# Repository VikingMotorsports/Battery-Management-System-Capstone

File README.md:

# VMS Battery Management Capstone 2026 Repo

All System Architecture KiCAD Schematics and GERBER files along with the zephyr firmware C code.

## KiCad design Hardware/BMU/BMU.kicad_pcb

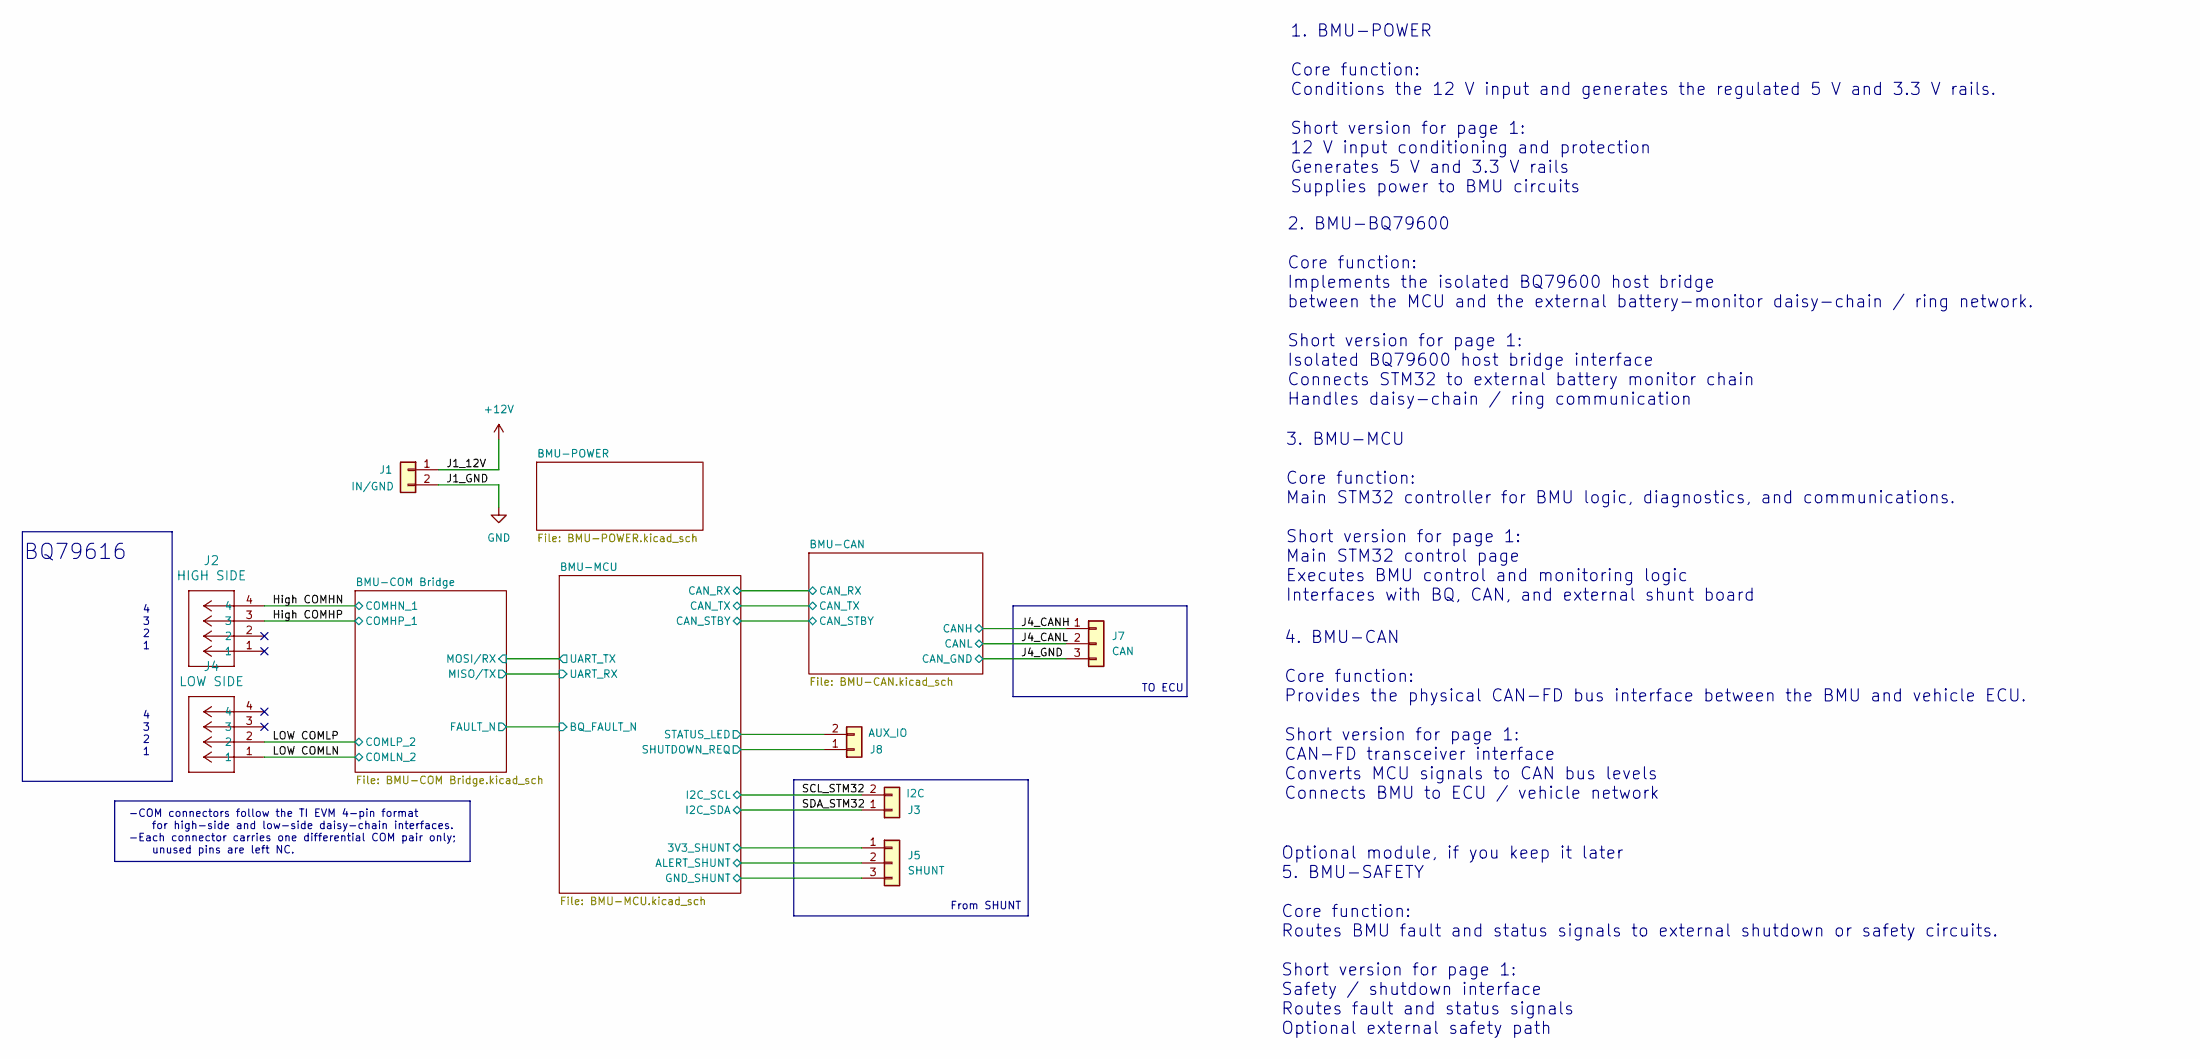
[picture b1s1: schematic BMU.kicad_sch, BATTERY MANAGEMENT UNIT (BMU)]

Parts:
J1: IN/GND; PinHeader_1x02_P2.54mm_Vertical
J2: HIGH SIDE; CONN_70551-xxxx_04_MOL
J3: I2C; PinHeader_1x02_P2.54mm_Vertical
J4: LOW SIDE; CONN_70551-xxxx_04_MOL
J5: SHUNT; PinHeader_1x03_P2.54mm_Vertical
J7: CAN; PinHeader_1x03_P2.54mm_Vertical
J8: AUX_IO; PinHeader_1x02_P2.54mm_Vertical

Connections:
+3V3: J5.1; also elsewhere on the board
+12V: J1.1; also elsewhere on the board
/BMU-MCU/ALERT_SHUNT: J5.2; also elsewhere on the board
/BMU-MCU/SHUTDOWN_REQ: J8.1; also elsewhere on the board
/BMU-MCU/STATUS_LED: J8.2; also elsewhere on the board
/High COMHN: J2.4; also elsewhere on the board
/High COMHP: J2.3; also elsewhere on the board
/J4_CANH: J7.1; also elsewhere on the board
/J4_CANL: J7.2; also elsewhere on the board
/LOW COMLN: J4.1; also elsewhere on the board
/LOW COMLP: J4.2; also elsewhere on the board
/SCL_STM32: J3.2; also elsewhere on the board
/SDA_STM32: J3.1; also elsewhere on the board
GND: J1.2, J5.3, J7.3; also elsewhere on the board

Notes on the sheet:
4 3 2 1
2. BMU-BQ79600 Core function: Implements the isolated BQ79600 host bridge between the MCU and the external battery-monitor daisy-chain / ring network. Short version for page 1: Isolated BQ79600 host bridge interface Connects STM32 to external battery monitor chain Handles daisy-chain / ring communi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
-COM connectors follow the TI EVM 4-pin format for high-side and low-side daisy-chain interfaces. -Each connector carries one differential COM pair only; unused pins are left NC.
4. BMU-CAN Core function: Provides the physical CAN-FD bus interface between the BMU and vehicle ECU. Short version for page 1: CAN-FD transceiver interface Converts MCU signals to CAN bus levels Connects BMU to ECU / vehicle network
3. BMU-MCU Core function: Main STM32 controller for BMU logic, diagnostics, and communications. Short version for page 1: Main STM32 control page Executes BMU control and monitoring logic Interfaces with BQ, CAN, and external shunt board
TO ECU
1. BMU-POWER Core function: Conditions the 12 V input and generates the regulated 5 V and 3.3 V rails. Short version for page 1: 12 V input conditioning and protection Generates 5 V and 3.3 V rails Supplies power to BMU circuits
From SHUNT
BQ79616
Optional module, if you keep it later 5. BMU-SAFETY Core function: Routes BMU fault and status signals to external shutdown or safety circuits. Short version for page 1: Safety / shutdown interface Routes fault and status signals Optional external safety path

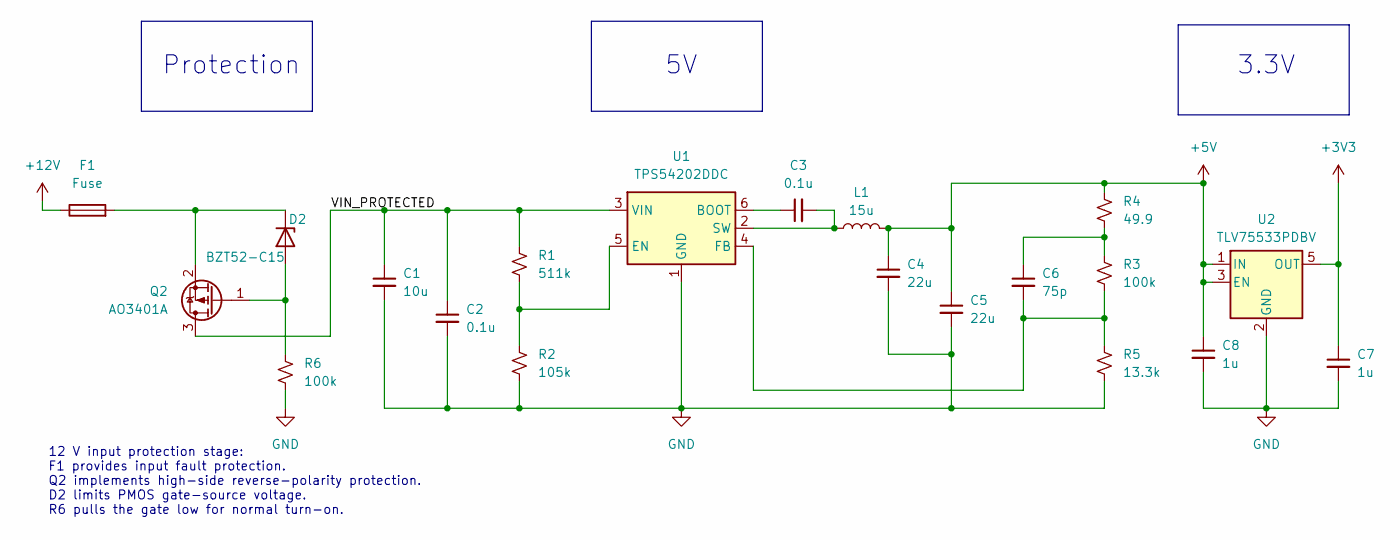
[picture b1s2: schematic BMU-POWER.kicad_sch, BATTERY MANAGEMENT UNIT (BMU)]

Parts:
C1: 10u; C_1206_3216Metric
C2, C3: 0.1u; C_0805_2012Metric
C4, C5: 22u; C_1206_3216Metric
C6: 75p; C_0805_2012Metric
C7, C8: 1u; C_0805_2012Metric
D2: BZT52-C15; D_SOD-123
F1: Fuse; Fuse_1206_3216Metric
L1: 15u; L_7.3x7.3_H4.5
Q2: AO3401A; SOT-23
R1: 511k; R_0805_2012Metric
R2: 105k; R_0805_2012Metric
R3, R6: 100k; R_0805_2012Metric
R4: 49.9; R_0805_2012Metric
R5: 13.3k; R_0805_2012Metric
U1: TPS54202DDC; SOT-23-6
U2: TLV75533PDBV; SOT-23-5

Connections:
+3V3: C7.1, U2.5 (OUT); also elsewhere on the board
+5V: C4.1, C5.1, C8.1, L1.2, R4.1, U2.1 (IN), U2.3 (EN); also elsewhere on the board
+12V: F1.1; also elsewhere on the board
/BMU-POWER/VIN_PROTECTED: C1.1, C2.1, Q2.3 (D), R1.1, U1.3 (VIN)
GND: C1.2, C2.2, C4.2, C5.2, C7.2, C8.2, R2.2, R5.2, R6.2, U1.1 (GND), U2.2 (GND); also elsewhere on the board
unnamed: C6.1, R3.1, R4.2
unnamed: D2.2 (A), Q2.1 (G), R6.1
unnamed: D2.1 (K), F1.2, Q2.2 (S)
unnamed: C3.1, U1.6 (BOOT)
unnamed: R1.2, R2.1, U1.5 (EN)
unnamed: C6.2, R3.2, R5.1, U1.4 (FB)
unnamed: C3.2, L1.1, U1.2 (SW)

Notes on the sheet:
3.3V
Protection
12 V input protection stage: F1 provides input fault protection. Q2 implements high-side reverse-polarity protection. D2 limits PMOS gate-source voltage. R6 pulls the gate low for normal turn-on.

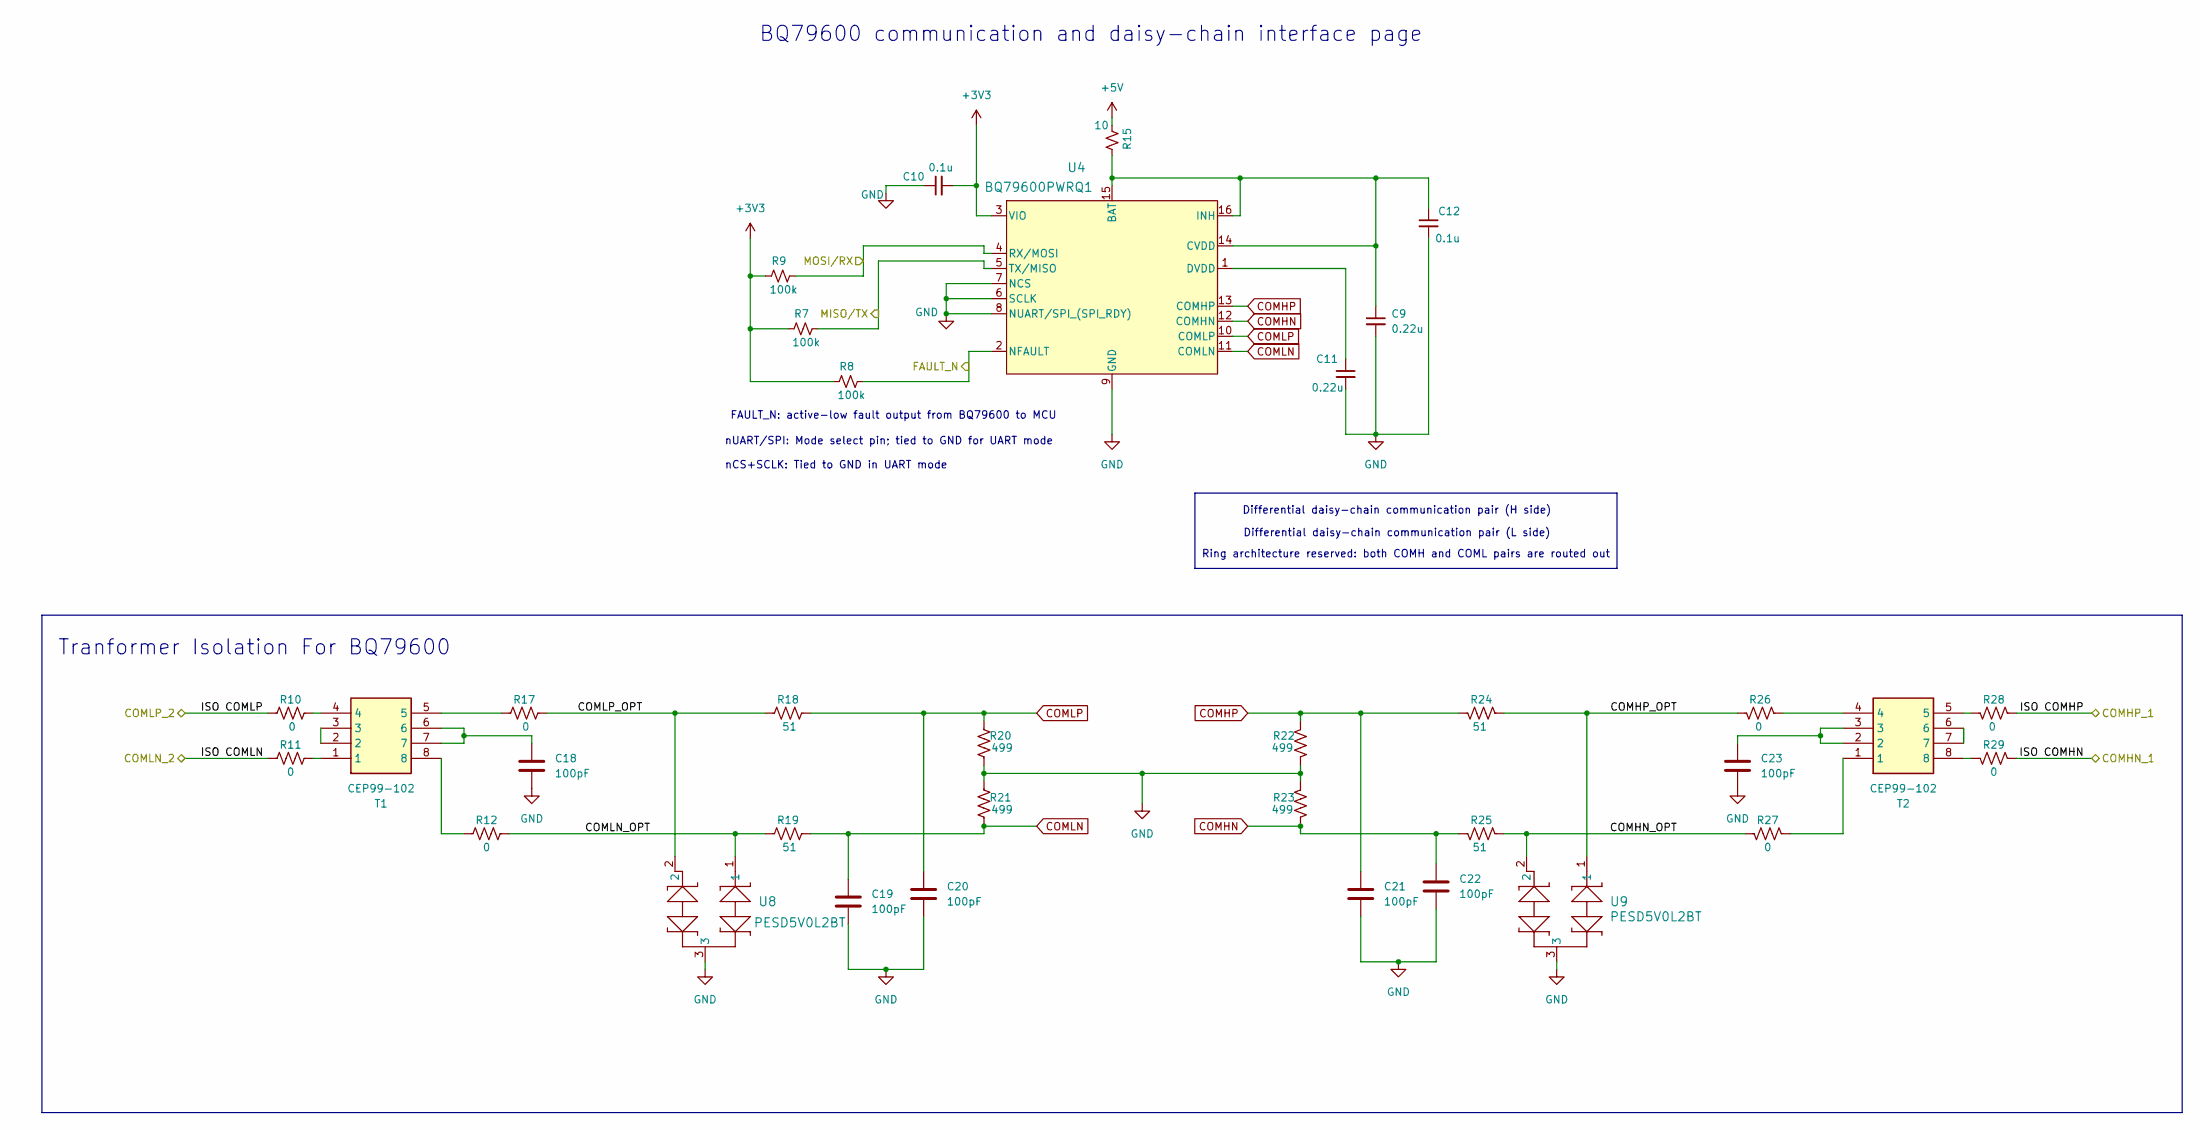
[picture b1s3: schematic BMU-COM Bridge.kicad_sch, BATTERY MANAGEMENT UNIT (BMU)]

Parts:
C9, C11: 0.22u; C_0805_2012Metric
C10, C12: 0.1u; C_0805_2012Metric
C18, C19, C20, C21, C22, C23: 100pF; C_0805_2012Metric
R7, R8, R9: 100k; R_0805_2012Metric
R10, R11, R12, R17, R26, R27, R28, R29: 0; R_0805_2012Metric
R15: 10; R_0805_2012Metric
R18, R19, R24, R25: 51; R_0805_2012Metric
R20, R21, R22, R23: 499; R_0805_2012Metric
T1, T2: CEP99-102; CEP99102; Manufacturer_Part_Number CEP99-102
U4: BQ79600PWRQ1; TSSOP16_PW_TEX
U8, U9: PESD5V0L2BT; SOT23_NEX

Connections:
+3V3: C10.2, R7.1, R8.1, R9.1, U4.3 (VIO); also elsewhere on the board
+5V: R15.1; also elsewhere on the board
/BMU-COM Bridge/COMHN_OPT: R25.1, R27.2, U9.2
/BMU-COM Bridge/COMHP_OPT: R24.1, R26.2, U9.1
/BMU-COM Bridge/COMLN_OPT: R12.2, R19.1, U8.1
/BMU-COM Bridge/COMLP_OPT: R17.2, R18.1, U8.2
/BMU-COM Bridge/FAULT_N: R8.2, U4.2 (NFAULT); also elsewhere on the board
/BMU-COM Bridge/MISO/TX: R7.2, U4.5 (TX/MISO); also elsewhere on the board
/BMU-COM Bridge/MOSI/RX: R9.2, U4.4 (RX/MOSI); also elsewhere on the board
/High COMHN: R29.1; also elsewhere on the board
/High COMHP: R28.1; also elsewhere on the board
/LOW COMLN: R11.1; also elsewhere on the board
/LOW COMLP: R10.1; also elsewhere on the board
COMHN: C22.1, R23.2, R25.2, U4.12 (COMHN)
COMHP: C21.1, R22.1, R24.2, U4.13 (COMHP)
COMLN: C19.1, R19.2, R21.2, U4.11 (COMLN)
COMLP: C20.1, R18.2, R20.1, U4.10 (COMLP)
GND: C9.2, C10.1, C11.2, C12.2, C18.2, C19.2, C20.2, C21.2, C22.2, C23.2, R20.2, R21.1, R22.2, R23.1, U4.6 (SCLK), U4.7 (NCS), U4.8 (NUART/SPI_(SPI_RDY)), U4.9 (GND), U8.3, U9.3; also elsewhere on the board
unnamed: C18.1, T1.6, T1.7
unnamed: C23.1, T2.2, T2.3
unnamed: R10.2, T1.4
unnamed: R11.2, T1.1
unnamed: R12.1, T1.8
unnamed: R17.1, T1.5
unnamed: R26.1, T2.4
unnamed: R27.1, T2.1
unnamed: R28.2, T2.5
unnamed: R29.2, T2.8
unnamed: T1.2, T1.3
unnamed: T2.6, T2.7
unnamed: C9.1, C12.1, R15.2, U4.14 (CVDD), U4.15 (BAT), U4.16 (INH)
unnamed: C11.1, U4.1 (DVDD)

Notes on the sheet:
Differential daisy-chain communication pair (H side)
Tranformer Isolation For BQ79600
Differential daisy-chain communication pair (L side)
BQ79600 communication and daisy-chain interface page
Ring architecture reserved: both COMH and COML pairs are routed out
nUART/SPI: Mode select pin; tied to GND for UART mode
FAULT_N: active-low fault output from BQ79600 to MCU
nCS+SCLK: Tied to GND in UART mode

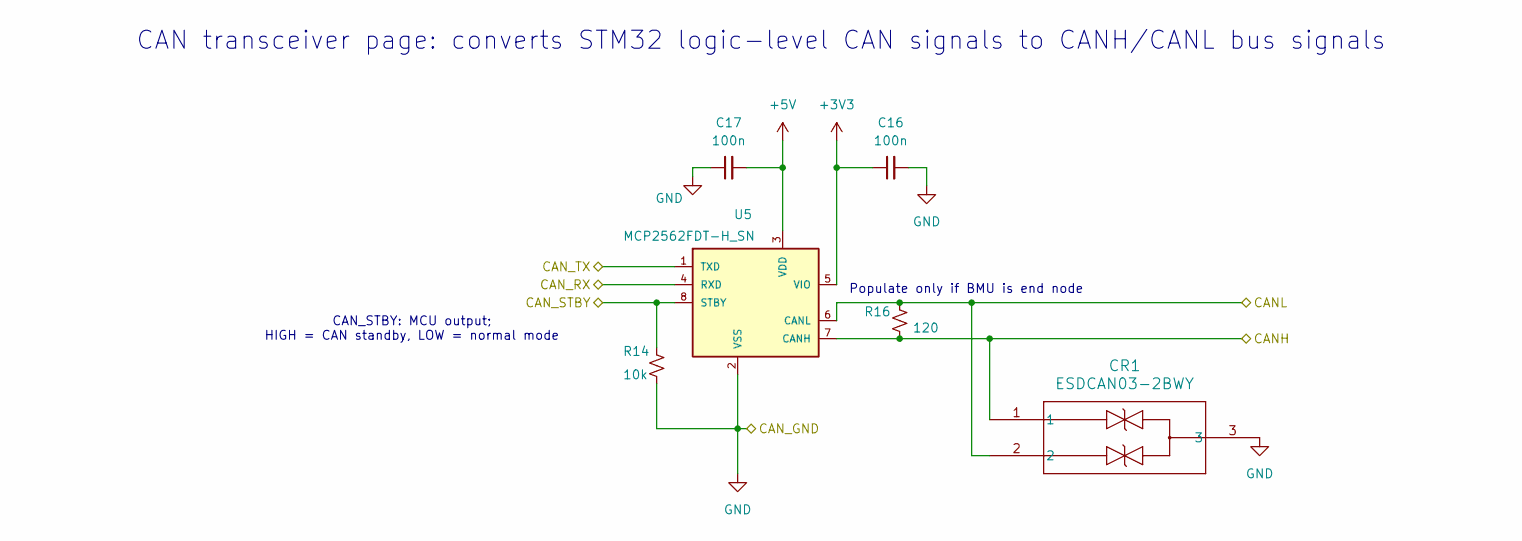
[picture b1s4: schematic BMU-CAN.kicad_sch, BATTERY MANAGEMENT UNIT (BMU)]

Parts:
C16, C17: 100n; C_0805_2012Metric
CR1: ESDCAN03-2BWY; SOT323-3L_STM
R14: 10k; R_0805_2012Metric
R16: 120; R_0805_2012Metric
U5: MCP2562FDT-H_SN; SOIC127P600X175-8N

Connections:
+3V3: C16.1, U5.5 (VIO); also elsewhere on the board
+5V: C17.2, U5.3 (VDD); also elsewhere on the board
/BMU-CAN/CAN_RX: U5.4 (RXD); also elsewhere on the board
/BMU-CAN/CAN_STBY: R14.1, U5.8 (STBY); also elsewhere on the board
/BMU-CAN/CAN_TX: U5.1 (TXD); also elsewhere on the board
/J4_CANH: CR1.1, R16.2, U5.7 (CANH); also elsewhere on the board
/J4_CANL: CR1.2, R16.1, U5.6 (CANL); also elsewhere on the board
GND: C16.2, C17.1, CR1.3, R14.2, U5.2 (VSS); also elsewhere on the board

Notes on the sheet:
CAN_STBY: MCU output; HIGH = CAN standby, LOW = normal mode
Populate only if BMU is end node
CAN transceiver page: converts STM32 logic-level CAN signals to CANH/CANL bus signals

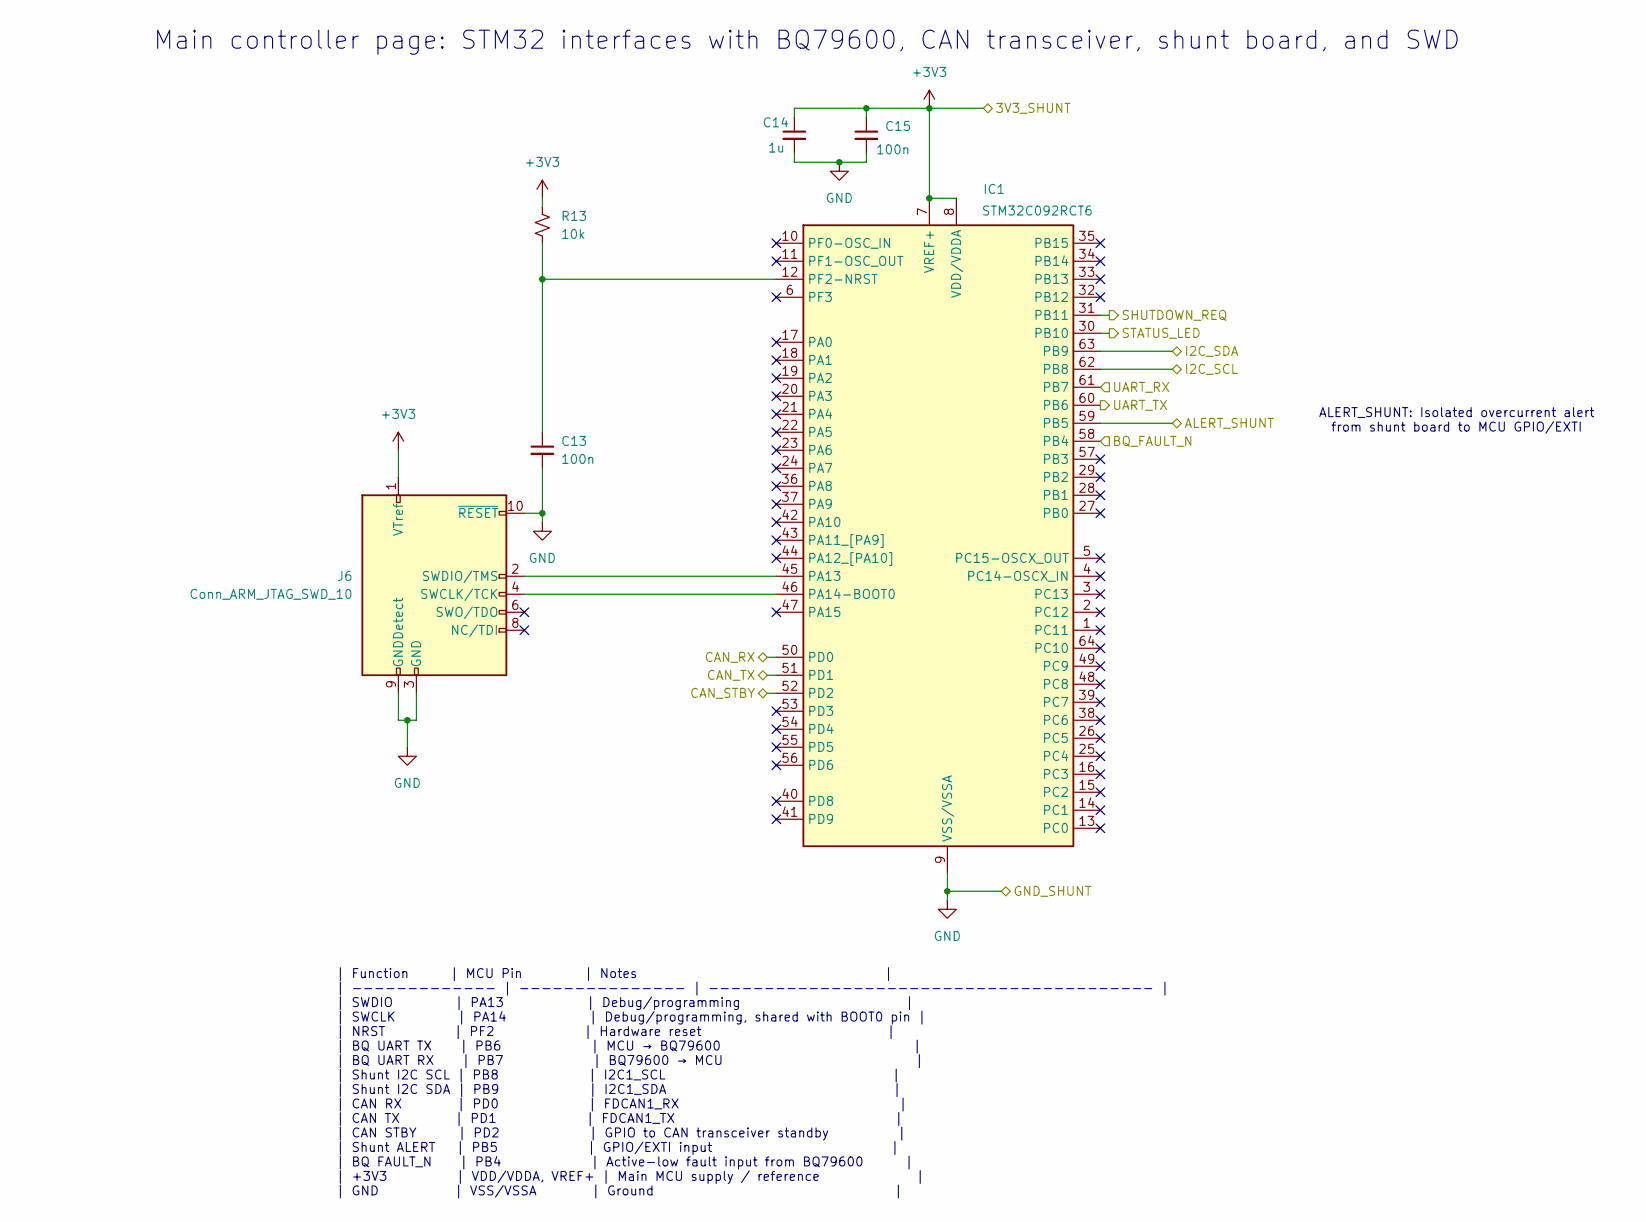
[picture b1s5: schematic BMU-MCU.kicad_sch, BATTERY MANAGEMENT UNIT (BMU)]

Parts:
C13, C15: 100n; C_0805_2012Metric
C14: 1u; C_0805_2012Metric
IC1: STM32C092RCT6; QFP50P1200X1200X160-64N; Manufacturer_Part_Number STM32C092RCT6; Mouser Part Number 511-STM32C092RCT6
J6: Conn_ARM_JTAG_SWD_10; PinHeader_2x05_P1.27mm_Vertical
R13: 10k; R_0805_2012Metric

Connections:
+3V3: C14.1, C15.1, IC1.7 (VREF+), IC1.8 (VDD/VDDA), J6.1 (VTref), R13.1; also elsewhere on the board
/BMU-CAN/CAN_RX: IC1.50 (PD0); also elsewhere on the board
/BMU-CAN/CAN_STBY: IC1.52 (PD2); also elsewhere on the board
/BMU-CAN/CAN_TX: IC1.51 (PD1); also elsewhere on the board
/BMU-COM Bridge/FAULT_N: IC1.58 (PB4); also elsewhere on the board
/BMU-COM Bridge/MISO/TX: IC1.61 (PB7); also elsewhere on the board
/BMU-COM Bridge/MOSI/RX: IC1.60 (PB6); also elsewhere on the board
/BMU-MCU/ALERT_SHUNT: IC1.59 (PB5); also elsewhere on the board
/BMU-MCU/SHUTDOWN_REQ: IC1.31 (PB11); also elsewhere on the board
/BMU-MCU/STATUS_LED: IC1.30 (PB10); also elsewhere on the board
/SCL_STM32: IC1.62 (PB8); also elsewhere on the board
/SDA_STM32: IC1.63 (PB9); also elsewhere on the board
GND: C13.2, C14.2, C15.2, IC1.9 (VSS/VSSA), J6.3 (GND), J6.5 (GND), J6.9 (GNDDetect), J6.10 (~RESET); also elsewhere on the board
unnamed: IC1.45 (PA13), J6.2 (SWDIO/TMS)
unnamed: IC1.46 (PA14-BOOT0), J6.4 (SWCLK/TCK)
unnamed: C13.1, IC1.12 (PF2-NRST), R13.2

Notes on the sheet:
| Function | MCU Pin | Notes | | ------------- | --------------- | ---------------------------------------- | | SWDIO | PA13 | Debug/programming | | SWCLK | PA14 | Debug/programming, shared with BOOT0 pin | | NRST | PF2 | Hardware reset | | BQ UART TX | PB6 | MCU → BQ79600 | | BQ UART RX | PB7 | BQ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
Main controller page: STM32 interfaces with BQ79600, CAN transceiver, shunt board, and SWD
ALERT_SHUNT: Isolated overcurrent alert from shunt board to MCU GPIO/EXTI

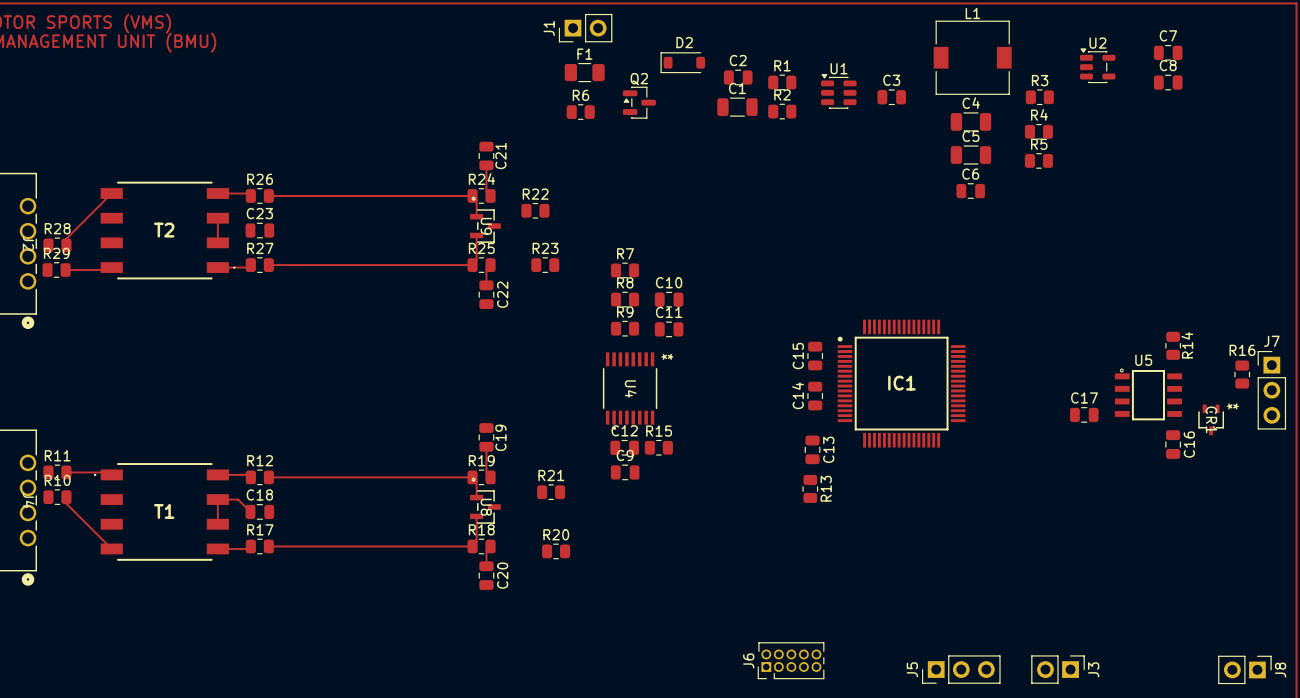
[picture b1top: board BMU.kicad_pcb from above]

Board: 4 copper layers, 74 parts (0 on the bottom side), 54 nets.

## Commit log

2026-03-31 Add BQ79600 wake and shutdown wake-up app
2026-04-01 Documentation and Hardware License added
2026-04-03 Hardware Schematics Added
2026-04-16 Minor Changes
2026-04-17 Add BMS monitor with UART, frame protocol, initialization, and cell voltage monitoring
2026-04-17 Clean up git ignore rules and remove macOS metadata files
2026-04-19 Add BMU schematic sheets
2026-04-20 Hardware Directory Reorganization
2026-04-21 update CAN and SHUNT IF
2026-04-21 Current SHUNT module added
2026-04-21 Hardware Projects Organized
2026-04-21 change CAN
2026-04-22 add comment
2026-04-22 Added Zephyr logging for error/status recording
2026-04-22 add footprint
2026-04-23 add iso
2026-04-23 .gitignore updated
2026-04-24 Added temperature monitoring for on board NTC thermistors
2026-04-25 update bmu
2026-04-28 layout
2026-04-28 CAN partitioning
2026-04-30 Test Plan Rough Draft
2026-06-29 Final Report with Team Members' email addresses added
